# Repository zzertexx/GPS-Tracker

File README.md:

# GPS Tracker
### Use this bracelet to get live location and watch on any device 
> do not use to stalk people by giving them "unsuspicious" bracelet and looking where they are!!

## Zine

## Images

## How to use?
1. Order components from Bill of Materials and 3D Print case
2. Solder electronics and assembly into case
3. Insert SIM-Card with cellular data over 2G 
4. place your parameters in firmware "modem.h" line 5 and 8
5. Open Firmware via nRF connect in VS Code using Add existing application
6. Add build configuration: board: nRF52dk_nRF52832
7. Wait for build -> connect to board via SWD: github.com/AndruPol/nrf52832-recover

## Features
* Button to Sleep/Wake
* LED indicator of work status
* BLE advertising for future app
* Send location data to personal Google Sheet
* Charge with Type-C
* Compatible with lots of watch straps

> In current version, software may have significant bugs, improper code, not enough features, but I will edit/fix as I get hardware to debug

## 4-layer PCB
**Built in KiCad 10.99 night build**
> You can't export 3D model in default KiCad 10.0.3 because of error   
Ignore User.Comments

1 Layer - F.Cu  
2 Layer - 3.3V  
3 Layer - GND  
4 Layer - B.Cu  

## Why did I build it?
My bro asked me if I can build one. I don't have any interest for GPS locators, or needness for one. I just wanted to try myself in designing Wearable and also help my bro, so I did it and I felt real hardship of building in limited space. Currently my design is really bad and MUST be fixed in next updates by tightening free space. 

## Bill of Materials
| Name | Quantity |
| --- | --- |
| nRF52832 | x1 |
| CH340C | x1 |
| USB-C 14 pin | x1 |
| TP4056-42-ESOP8 | x1 |
| FS8205A | x1 |
| DW01A | x1 |
| XC6206P332MR-G | x1 |
| TXS0102DCUR | x1 |
| XUNPU SMN-303 | x1
| A7680C-LANV | x1 |
| ZIISOR TX4G-FPC-4015 | x1 |
| 16-213SURC/S530-A4/TR8 | x1 |
| 2450AT18A100E | x1 |
| NX2016SA-32MHZ | x1 |
| SC-20S,32.768kHz | x1 |
| BLM21PG300SN1D | x1 |
| ESDBW5V0A1 | x1 |
| LXES15AAA1-153 | x1 |
| L80-R | x1 |
| 500 mAh 503040 Battery | x1 |
| Straps - Galaxy watch 6 18mm | x1 |
| ST-LINK V2 | x1 |
| B3U-3000P LED Diode | x1 |
| LXES15AAA1-153 | x1 |
| 100nF C | x14 |
| 10uF C | x2 |
| 1uF C | x4 |
| 12pF C | x6 |
| 100uF C | x2 |
| 4.7uF C | x1 |
| 0.8pF C | x1 |
| 10pF C | x1 |
| 33pF C | x1 |
| 100pF C | x1 |
| 10pF C | x1 |
| 1.2K R | x1 |
| 1K R | x3 |
| 100 R | x5 |
| 5.1K R | x2 |
| 10K R | x1 |
| 0 R | x1 |
| 10uH L | x1 |
| 3.9nH L | x1 |
| 15nH L | x1 |
| M2 Screws | x8 |

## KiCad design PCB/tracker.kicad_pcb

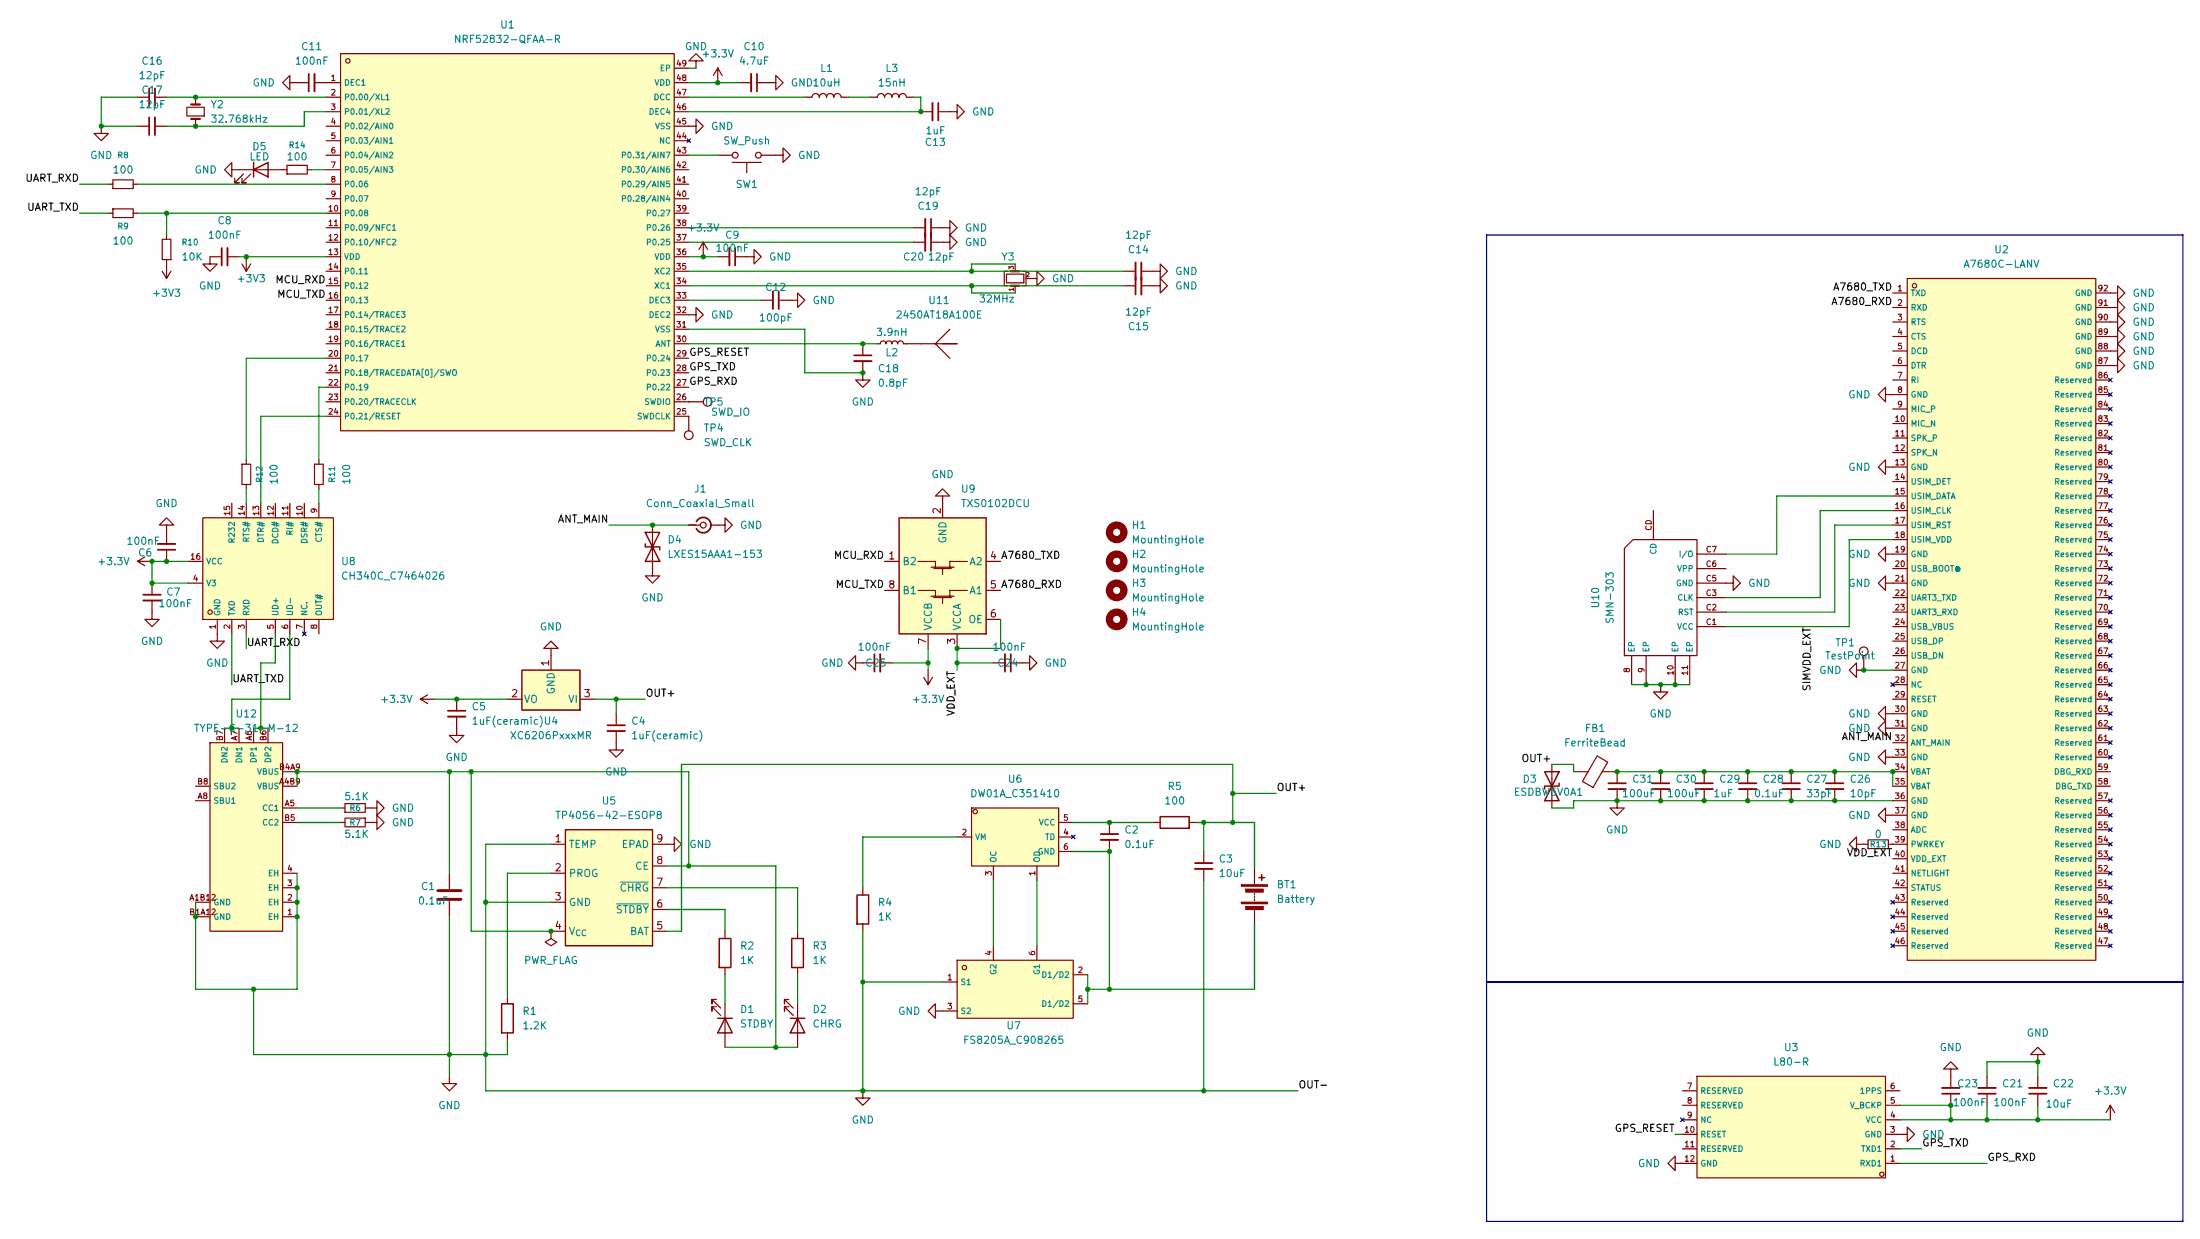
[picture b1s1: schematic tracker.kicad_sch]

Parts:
BT1: Battery; JST_PH_S2B-PH-K_1x02_P2.00mm_Horizontal
C1, C2, C28: 0.1uF; C_0402_1005Metric
C3, C22: 10uF; C_0603_1608Metric
C4, C5: 1uF(ceramic); C_0603_1608Metric
C6, C7, C8, C9, C11, C21, C23, C24, C25: 100nF; C_0402_1005Metric
C10: 4.7uF; C_0603_1608Metric
C12: 100pF; C_0402_1005Metric
C13, C29: 1uF; C_0603_1608Metric
C14, C15, C16, C17, C19, C20: 12pF; C_0402_1005Metric
C18: 0.8pF; C_0603_1608Metric_Pad1.08x0.95mm_HandSolder
C26: 10pF; C_0402_1005Metric
C27: 33pF; C_0402_1005Metric
C30, C31: 100uF; CP_Elec_5x5.4
D1: STDBY; LED_0402_1005Metric_Pad0.77x0.64mm_HandSolder
D2: CHRG; LED_0402_1005Metric_Pad0.77x0.64mm_HandSolder
D3: ESDBW5V0A1; D_0402_1005Metric
D4: LXES15AAA1-153; D_0402_1005Metric
D5: LED; LED_Kingbright_APA1606_1.6x0.6mm_Horizontal
FB1: FerriteBead; L0805
H1, H2, H3, H4: MountingHole; MountingHole_2.2mm_M2
J1: Conn_Coaxial_Small; U.FL_Hirose_U.FL-R-SMT-1_Vertical
L1: 10uH; L_0805_2012Metric
L2: 3.9nH; L_0402_1005Metric
L3: 15nH; L_0402_1005Metric
R1: 1.2K; R_0603_1608Metric
R2, R3, R4: 1K; R_0402_1005Metric
R5, R8, R9, R11, R12: 100; R_0402_1005Metric
R6, R7: 5.1K; R_0402_1005Metric
R10: 10K; R_0805_2012Metric
R13: 0; R_0402_1005Metric
R14: 100; C_0402_1005Metric
SW1: SW_Push; KEY-SMD_B3U-3000P
TP1: TestPoint; TestPoint_Pad_D1.5mm
TP4: SWD_CLK; TestPoint_Pad_D1.5mm
TP5: SWD_IO; TestPoint_Pad_D1.5mm
U1: NRF52832-QFAA-R; QFN-48_L6.0-W6.0-P0.40-BL-EP3.8; LCSC C77540
U2: A7680C-LANV; LCC-LAG_L17.6-W15.7_A7680C; LCSC C5381968
U3: L80-R; GPSM-SMD_L80-R; LCSC C188357
U4: XC6206PxxxMR; SOT-23-3
U5: TP4056-42-ESOP8; SOIC-8-1EP_3.9x4.9mm_P1.27mm_EP2.41x3.3mm_ThermalVias
U6: DW01A_C351410; SOT-23-6_L2.9-W1.6-P0.95-LS2.8-BL; LCSC C351410
U7: FS8205A_C908265; SOT-23-6_L2.9-W1.6-P0.95-LS2.8-BR; LCSC C908265
U8: CH340C_C7464026; SOP-16_L10.0-W3.9-P1.27-LS6.0-BL; LCSC C7464026
U9: TXS0102DCU; VSSOP-8_2.3x2mm_P0.5mm
U10: SMN-303; SIM-SMD_SMN-303; LCSC C266888
U11: 2450AT18A100E; ANT-SMD_L3.2-W1.6; LCSC C89334
U12: TYPE-C-31-M-12; USB-C_SMD-TYPE-C-31-M-12_1; LCSC C165948
Y2: 32.768kHz; OSC-SMD_L2.0-W1.2
Y3: 32MHz; CRYSTAL-SMD_4P-L2.0-W1.6-BL

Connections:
+3.3V: C5.1, C6.1, C7.1, C9.2, C10.2, C21.1, C22.1, C23.1, C25.2, U1.36 (VDD), U1.48 (VDD), U3.4 (VCC), U3.5 (V_BCKP), U4.2 (VO), U8.4 (V3), U8.16 (VCC), U9.7 (VCCB)
+3V3: C8.2, R10.1, U1.13 (VDD)
/A7680_RXD: U2.2 (RXD), U9.5 (A1)
/A7680_TXD: U2.1 (TXD), U9.4 (A2)
/ANT_MAIN: D4.2 (A2), J1.1 (In), U2.32 (ANT_MAIN)
/GPS_RESET: U1.29 (P0.24), U3.10 (RESET)
/GPS_RXD: U1.27 (P0.22), U3.1 (RXD1)
/GPS_TXD: U1.28 (P0.23), U3.2 (TXD1)
/MCU_RXD: U1.15 (P0.12), U9.1 (B2)
/MCU_TXD: U1.16 (P0.13), U9.8 (B1)
/OUT+: BT1.1 (+), C3.1, C4.1, D3.2 (A2), FB1.1, R5.2, U4.3 (VI), U5.5 (BAT)
/SIMVDD_EXT: U2.18 (USIM_VDD), U10.C1 (VCC)
/UART_RXD: R8.1, U8.3 (RXD)
/UART_TXD: R9.1, U8.2 (TXD)
/VDD_EXT: C24.2, U2.40 (VDD_EXT), U9.3 (VCCA), U9.6 (OE)
GND: C1.2, C3.2, C4.2, C5.2, C6.2, C7.2, C8.1, C9.1, C10.1, C11.1, C12.1, C13.1, C14.1, C15.2, C16.1, C17.1, C18.2, C19.1, C20.1, C21.2, C22.2, C23.2, C24.1, C25.1, C26.2, C27.2, C28.2, C29.2, C30.2, C31.2, D3.1 (A1), D4.1 (A1), D5.1 (K), J1.2 (Ext), R1.2, R4.2, R6.2, R7.1, R13.1, SW1.1, TP1.1 (1_1), U1.31 (VSS), U1.32 (DEC2), U1.45 (VSS), U1.49 (EP), U2.8 (GND), U2.13 (GND), U2.19 (GND), U2.21 (GND), U2.27 (GND), U2.30 (GND), U2.31 (GND), U2.33 (GND), U2.36 (GND), U2.37 (GND), U2.87 (GND), U2.88 (GND), U2.89 (GND), U2.90 (GND), U2.91 (GND), U2.92 (GND), U3.3 (GND), U3.12 (GND), U4.1 (GND), U5.1 (TEMP), U5.3 (GND), U5.9 (EPAD), U7.1 (S1), U7.3 (S2), U8.1 (GND), U9.2 (GND), U10.8 (EP), U10.9 (EP), U10.10 (EP), U10.11 (EP), U10.C5 (GND), U12.1 (EH), U12.2 (EH), U12.3 (EH), U12.4 (EH), U12.A1B12 (GND), U12.B1A12 (GND), Y3.2 (G), Y3.4 (G)
unnamed: BT1.2 (-), C2.2, U6.6 (GND), U7.2 (D1/D2), U7.5 (D1/D2)
unnamed: C26.1, C27.1, C28.1, C29.1, C30.1, C31.1, FB1.2, U2.34 (VBAT), U2.35 (VBAT)
unnamed: C1.1, D1.2 (A), D2.2 (A), U5.4 (V_{CC}), U5.8 (CE), U12.A4B9 (VBUS), U12.B4A9 (VBUS)
unnamed: D1.1 (K), R2.2
unnamed: D2.1 (K), R3.2
unnamed: D5.2 (A), R14.1
unnamed: L1.2, L3.1
unnamed: C18.1, L2.1, U1.30 (ANT)
unnamed: L1.1, U1.47 (DCC)
unnamed: C11.2, U1.1 (DEC1)
unnamed: C12.2, U1.33 (DEC3)
unnamed: C13.2, L3.2, U1.46 (DEC4)
unnamed: C16.2, U1.2 (P0.00/XL1), Y2.2
unnamed: C17.2, U1.3 (P0.01/XL2), Y2.1
unnamed: R14.2, U1.7 (P0.05/AIN3)
unnamed: R8.2, U1.8 (P0.06)
unnamed: R9.2, R10.2, U1.10 (P0.08)
unnamed: R12.1, U1.20 (P0.17)
unnamed: R11.1, U1.22 (P0.19)
unnamed: U1.24 (P0.21/RESET), U8.13 (DTR#)
unnamed: C20.2, U1.37 (P0.25)
unnamed: C19.2, U1.38 (P0.26)
unnamed: SW1.2, U1.43 (P0.31/AIN7)
unnamed: TP4.1 (1_1), U1.25 (SWDCLK)
unnamed: TP5.1 (1_1), U1.26 (SWDIO)
unnamed: C15.1, U1.34 (XC1), Y3.1
unnamed: C14.2, U1.35 (XC2), Y3.3
unnamed: R13.2, U2.39 (PWRKEY)
unnamed: R1.1, U5.2 (PROG)
unnamed: R3.1, U5.7 (~CHRG)
unnamed: R2.1, U5.6 (~STDBY)
unnamed: U6.3 (OC), U7.4 (G2)
unnamed: U6.1 (OD), U7.6 (G1)
unnamed: C2.1, R5.1, U6.5 (VCC)
unnamed: R4.1, U6.2 (VM)
unnamed: R11.2, U8.9 (CTS#)
unnamed: R12.2, U8.14 (RTS#)
unnamed: U2.16 (USIM_CLK), U10.C3 (CLK)
unnamed: U2.15 (USIM_DATA), U10.C7 (I/O)
unnamed: U2.17 (USIM_RST), U10.C2 (RST)
unnamed: L2.2, U11.1 (ANT_1)
unnamed: R6.1, U12.A5 (CC1)
unnamed: R7.2, U12.B5 (CC2)
unnamed: U8.6 (UD-), U12.A7 (DN1), U12.B7 (DN2)
unnamed: U8.5 (UD+), U12.A6 (DP1), U12.B6 (DP2)

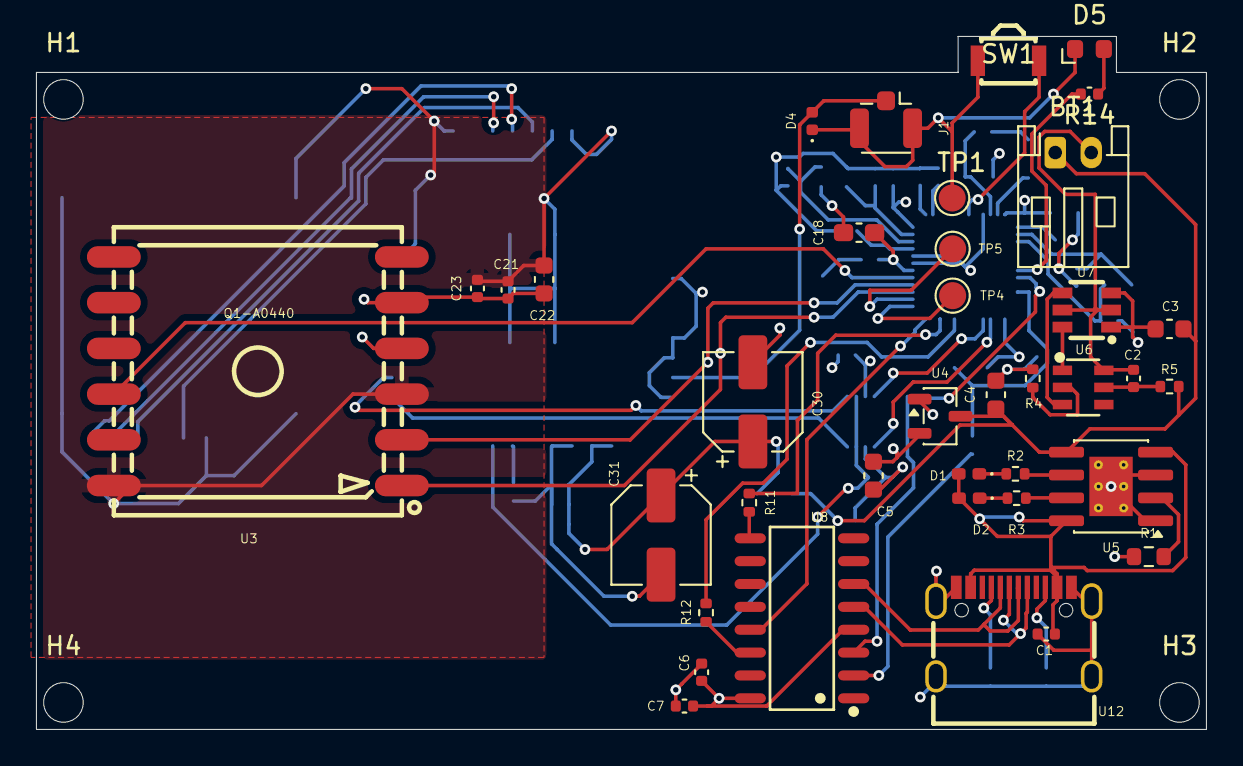
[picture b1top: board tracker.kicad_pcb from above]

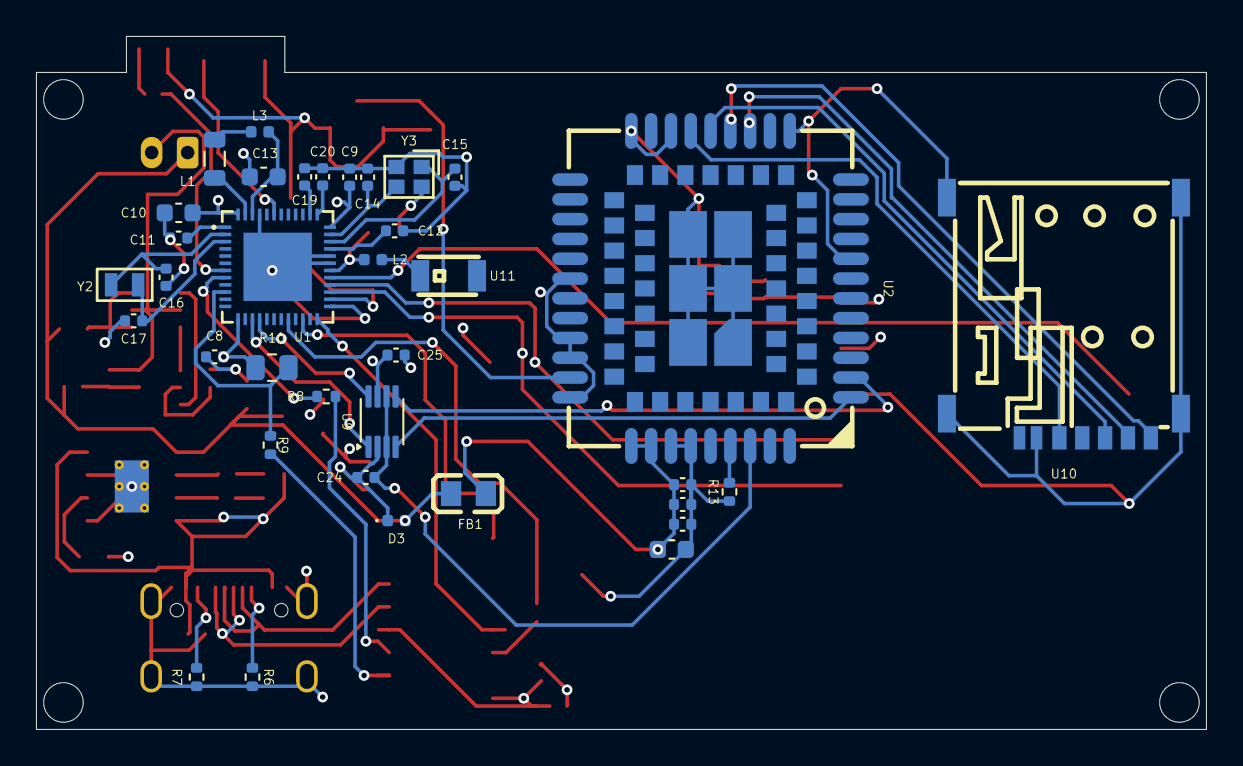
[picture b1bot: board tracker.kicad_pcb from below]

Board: 4 copper layers, 65.0 x 38.5 mm, 78 parts (36 on the bottom side), 61 nets.
